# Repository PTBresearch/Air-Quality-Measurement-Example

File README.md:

# Note: This repository is meant as an example. The code is incomplete and not the latest version. 

# Note: The global InfluxDB instance is planned to be replaced by Fiware.

# Air Quality

## Sensors List (Not Complete)

+ **PPD42NS** (Dust Concentration)

+ **BME280** (Humidity, Air Pressure, Temperature)

+ **CCS811** (TVOC Value, CO2 Equivalent)

+ **MAX31855PMB1#** (Temperature)

+ **SHT35** (Temperature, Humidity)

+ **GUVA-S12D** (UV)

+ **TCS34725** Light Sensor (RGB, Color Temperature, Brightness, Reference Value)

+ **MH-Z19C** (CO2 Value Infrared Sensor, Temperature)

+ **SPH** (DB)

+ **HP206C** ()

## Images and Render

<table>
  <tr>
    <td>
      
      <figcaption>Blender Case with PCB Render</figcaption>
    </td>
    <td>
      
      <figcaption>Blender Base with PCB Render</figcaption>
    </td>
    <td>
      
      <figcaption>Blender PCB Render</figcaption>
    </td>
  </tr>
  <tr>
    <td>
      
      <figcaption>Full Top</figcaption>
    </td>
    <td>
      
      <figcaption>Full Front</figcaption>
    </td>
    <td>
      
      <figcaption>Sensor Station</figcaption>
    </td>
  </tr>
  <tr>
    <td>
      
      <figcaption>Open PCB V1</figcaption>
    </td>
    <td>
      
      <figcaption>Front View</figcaption>
    </td>
    <td>
      
      <figcaption>Side View</figcaption>
    </td>
  </tr>
</table>

## Structure

```
.
├── Arduino-Code/          # The main folder for all microcontroller code.
│   ├── Main/              # Code for the primary Arduino prototype (likely ESP8266).
│   │   ├── lib/           # Libraries for this specific project.
│   │   └── Main.ino # The main program file for the Arduino.
│
├── Dokumentation/         # Images.
│
├── Files/                 # Specific files relevant to hardware and measurements.
│   ├── Gehaeuse/          # 3D models and design files for the project's enclosure.
│   └── Platinen/          # Design files (Gerber files, etc.) for the printed circuit boards (PCBs).
│
└── Raspberry-Installer/   # Scripts and files for setting up the Raspberry Pi.
    └── Docker/            # Docker configurations and source code for installing services on the Pi.
        └── src/           # Source code used by the Docker containers.
```

## Function

```
┌── Raspberry Pi
│   └── Creates a Wi-Fi network
│
└── Arduino
    ├── Connects to the Wi-Fi network
    │
    ├── Reads data from the sensor
    │
    └── Sends data over Wi-Fi to the API
        │
        └── API
            ├── Collects the sent data
            │
            ├── Inserts the data into a local database (InfluxDB)
            │
            └── Inserts the data into a global database (InfluxDB)
```

## Example JSON-Structure

```
{
  "arduino_board": "<arduino_id>",
  "sensors": [
    {
      "name": "<sensor_name>",
      "sensor_model": "<sensor_model>",
      "readings": [
        {
          "type": "<influx measurement>",
          "value": VALUE,
          "unit": "<unit>"
          "label": "<label optional>"
        },
        {
          "type": "<influx measurement>",
          "value": VALUE,
          "unit": "<unit>"
          "label": "<label optional>"
        }
      ]
    },
    {
      "name": "bme280",
      "sensor_model": "",
      "readings": [
        {
          "type": "temperature",
          "value": VALUE,
          "unit": "celsius"
        },
        {
          "type": "pressure",
          "value": VALUE,
          "unit": "hpa"
        },
        {
          "type": "humidity",
          "value": VALUE,
          "unit": "%"
        }
      ]
    }
  ]
}
```

---

## Instalation

1. Download: 

```bash
git clone <url> luftqualitaet
```

2. Edit ```WLAN_SSID``` in ```luftqualitaet/Raspberry-Installer/config.sh``` 
```bash
export replace=<Hostname>
sed -i -e 's/WLAN_SSID = Hostname/WLAN_SSID = ${replace}/g' luftqualitaet/Raspberry-Installer/config.sh
```

3. (Optional) Set Proxy Settings ```luftqualitaet/Raspberry-Installer/Docker/.env```
```bash
echo "http_proxy=http://webproxy:8080
https_proxy=http://webproxy:8080
no_proxy=influx,localhost" > /home/pi/luftqualitaet/Raspberry-Installer/Docker/.env
```

4. Login as Root
```bash
sudo -i
```

5. Change directory to Installer Location
```bash
cd /home/pi/luftqualitaet/Raspberry-Installer
```

6. Make Script executeable
```bash
chmod +x config.sh setup.sh
```

7. Set Current Time
```bash
HTTP_DATE=$(curl -x http://webproxy:8080  -ksI 'https://ptb.de' | grep -i '^date:' | sed 's/Date: //i' | sed 's/ (GMT)//')
if [ -n "$HTTP_DATE" ]; then date -s "$HTTP_DATE" && echo "Systemzeit erfolgreich gesetzt."; else echo "WARNUNG: Konnte die Zeit nicht über HTTP abrufen."; fi
```

8. Run Script
```
./setup.sh
```

9. Change directory to Docker Location
```bash
cd /home/pi/luftqualitaet/Raspberry-Installer/Docker
```

10. Start Docker
```bash
docker compose up -d
```

11. Setup Influxdb (http://hostname:8086) and Grafan (http://hostname:3000) 

12. Set InfluxDB Token in Config ```/home/pi/Raspberry-Installer/Docker/src/config.yml````

13. Restart Docker
```bash
docker compose down
docker compose up -d
```

14. Restart Raspberry PI
```bash
systemctl reboot
```

---

## Components

### Raspberry PI

| Component | Order Link | Datasheet Link(s) | Further Information |
|---|---|---|---|
| Pi 4B | [https://www.reichelt.de/das-reichelt-raspberry-pi-4-b-4-gb-all-in-bundle-rpi-4b-4gb-allin-p263086.html](https://www.reichelt.de/das-reichelt-raspberry-pi-4-b-4-gb-all-in-bundle-rpi-4b-4gb-allin-p263086.html) | | |
| Micro SD | [https://www.reichelt.de/de/de/shop/produkt/microsdxc-speicherkarte_128gb_samsung_pro_plus-313955](https://www.reichelt.de/de/de/shop/produkt/microsdxc-speicherkarte_128gb_samsung_pro_plus-313955) | | |
| GPS | [https://www.reichelt.de/de/de/shop/produkt/raspberry_pi_shield_-_multi-gnss_l76x-266060](https://www.reichelt.de/de/de/shop/produkt/raspberry_pi_shield_-_multi-gnss_l76x-266060) | | |
| Raspberry Pi Shield | [https://www.reichelt.de/de/de/shop/produkt/raspberry_pi_shield_-_display_lcd-touch_7_800x480_pixel-282508](https://www.reichelt.de/de/de/shop/produkt/raspberry_pi_shield_-_display_lcd-touch_7_800x480_pixel-282508) | | |

### Sensor Station

| Component | Sensor Type | Order Link | Datasheet Link(s) | Notes | Ambient Temperature | Humidity | Air Pressure |
|---|---|---|---|---|---|---|---|
| **BME280** | Temp & Pressure Sensor | [https://www.reichelt.de/ch/de/shop/produkt/entwicklerboards\_-\_temperatur-\_feuchtigkeits-*und\_drucksensor*-253982](https://www.reichelt.de/ch/de/shop/produkt/entwicklerboards_-_temperatur-_feuchtigkeits-_und_drucksensor_-253982) | [https://cdn-reichelt.de/documents/datenblatt/A300/BST-BME280-DS002-1509607.pdf](https://cdn-reichelt.de/documents/datenblatt/A300/BST-BME280-DS002-1509607.pdf) | Inaccurate temperature (error tolerance of +3°C) | Accuracy: +1.0°C \<br\> Range: -40°C to +85°C \<br\> Max Deviation: Up to +1.5°C | Accuracy: +3% rF \<br\> Range: 0% to 100% rF \<br\> Max Deviation: up to +5% | Accuracy: +1 hPa \<br\> Range: 300 hPa \<br\> Max Deviation: Up to +1.7 hPa |
| **CCS811** | TVOC | [https://www.reichelt.de/ch/de/shop/produkt/entwicklerboards\_-\_sensor\_fuer\_luftqualitaet\_ccs811-253655](https://www.reichelt.de/ch/de/shop/produkt/entwicklerboards_-_sensor_fuer_luftqualitaet_ccs811-253655) | [https://cdn-reichelt.de/documents/datenblatt/A300/SEN-CCS811V1-DATENBLATT-02-11-2020.pdf](https://cdn-reichelt.de/documents/datenblatt/A300/SEN-CCS811V1-DATENBLATT-02-11-2020.pdf) | Has a burn-in period (48 hours) and a warm-up time (20 min) before it becomes accurate | Accuracy: +3°C \<br\> Range: 0°C to +50°C \<br\> Max Deviation: approx. +5°C | Range: 10% to 95% | |
| **PPD42NS** | Dust | [https://www.reichelt.de/ch/de/shop/produkt/arduino\_-\_staubsensor\_ppd42ns-191264](https://www.reichelt.de/ch/de/shop/produkt/arduino_-_staubsensor_ppd42ns-191264) | [https://cdn-reichelt.de/documents/datenblatt/A300/101020012\_01.pdf](https://cdn-reichelt.de/documents/datenblatt/A300/101020012_01.pdf) | Must be straight, requires 3 min to warm up, arbitrary operation can lead to damage, standard settings should not be changed | Recommended Range: -10°C to +65°C | Range: 0% to 70% | |
| **MAX31855PMB1\#** | Typk Temp | [https://de.farnell.com/analog-devices/max31855pmb1/peripheriemodul-thermoel-digit/dp/2530496](https://de.farnell.com/analog-devices/max31855pmb1/peripheriemodul-thermoel-digit/dp/2530496) | [https://www.farnell.com/datasheets/2025616.pdf](https://www.farnell.com/datasheets/2025616.pdf) | Inaccurate temperature (error tolerance of +2°C) | Recommended Range: -20°C to +85°C | Range: 0% to 95% | |
| **D1 Mini** | D1 Mini | [https://www.reichelt.de/de/de/shop/produkt/d1\_mini\_-\_kompatibles\_esp8266\_board\_v2\_0-253978](https://www.reichelt.de/de/de/shop/produkt/d1_mini_-_kompatibles_esp8266_board_v2_0-253978) | | | | | |
| **D1 Mini** | D1 Mini Pro | https:www.reichelt.de/de/de/shop/produkt/d1\_mini\_pro\_-\_kompatibles\_esp8266\_board\_cp2104-266066 | | | | | |
| **Power Supply** | Breadboard | [https://www.reichelt.de/de/de/shop/produkt/entwicklerboards\_-\_spannungsversorgung\_f\_steckboards-202832](https://www.reichelt.de/de/de/shop/produkt/entwicklerboards_-_spannungsversorgung_f_steckboards-202832) | [https://cdn-reichelt.de/documents/datenblatt/A300/DATENBLATTSBC-POW-BB.pdf](https://cdn-reichelt.de/documents/datenblatt/A300/DATENBLATTSBC-POW-BB.pdf) | Too high voltage can damage the device or even lead to a fire | Recommended Range: 0°C to +70°C | Range: 10% to 60% (Absolutely not intended for humid rooms) | |
| **GSM18E09-P1J** | Plug-in Power Supply | [https://www.conrad.de/de/p/mean-well-gsm18e09-p1j-steckernetzteil-festspannung-9-v-dc-2-a-18-w-1837961.html](https://www.conrad.de/de/p/mean-well-gsm18e09-p1j-steckernetzteil-festspannung-9-v-dc-2-a-18-w-1837961.html) | [https://asset.conrad.com/media10/add/160267/c1/-/en/001837961DS01/datenblatt-1837961-mean-well-gsm18e09-p1j-steckernetzteil-festspannung-9-vdc-2-a-18-w.pdf](https://asset.conrad.com/media10/add/160267/c1/-/en/001837961DS01/datenblatt-1837961-mean-well-gsm18e09-p1j-steckernetzteil-festspannung-9-vdc-2-a-18-w.pdf) | Only lasts 3 years and is only 88% efficient | Recommended Range: -25 to +60 | Range: 20% to 90% | |
| **SHT35** | Temp & Humidity | [https://de.farnell.com/seeed-studio/101020212/sensorplatine-arduino-board/dp/3932104](https://de.farnell.com/seeed-studio/101020212/sensorplatine-arduino-board/dp/3932104) | [https://www.farnell.com/datasheets/3708357.pdf](https://www.farnell.com/datasheets/3708357.pdf) | Environmentally sensitive and should not be touched with fingers as it can be damaged | Recommended Range: -40°C to 125°C | Range: 10% to 90% | |
| **ADC** | Analog Digital Converter | [https://www.conrad.de/de/p/joy-it-ky053adc-raspberry-pi-erweiterungs-platine-passend-fuer-einplatinen-computer-raspberry-pi-raspberry-pi-a-b-1656368.html](https://www.conrad.de/de/p/joy-it-ky053adc-raspberry-pi-erweiterungs-platine-passend-fuer-einplatinen-computer-raspberry-pi-raspberry-pi-a-b-1656368.html) | [https://asset.conrad.com/media10/add/160267/c1/-/de/001656368DS01/datenblatt-1656368-joy-it-ky053adc-raspberry-pi-erweiterungs-platine-passend-fuer-einplatinen-computer-raspberry-pi-raspberry-pi-a-b.pdf](https://asset.conrad.com/media10/add/160267/c1/-/de/001656368DS01/datenblatt-1656368-joy-it-ky053adc-raspberry-pi-erweiterungs-platine-passend-fuer-einplatinen-computer-raspberry-pi-raspberry-pi-a-b.pdf) | Sensitive to interference due to its high resolution, which can make it slower to measure rapidly changing signals or values | Recommended Range: -40°C to 125°C | Range: 0% to 95% | |
| **GUVA-S12D** | UV Sensor | [https://www.reichelt.de/de/de/shop/produkt/arduino\_-\_uv-sensor\_guva-s12d-191215](https://www.reichelt.de/de/de/shop/produkt/arduino_-_uv-sensor_guva-s12d-191215) | [https://cdn-reichelt.de/documents/datenblatt/A300/101020043\_01.pdf](https://cdn-reichelt.de/documents/datenblatt/A300/101020043_01.pdf) | Can be altered by temperature, sensitive to environmental influences, not precise | Recommended Range: -30°C to +85°C | Range: 0% to 95% | |
| **TCS34725** | Light Sensor | [https://www.conrad.de/de/p/az-delivery-tcs34725-rgb-farb-sensor-mit-infrarot-filter-diy-modul-zur-farb-erkennung-kompatibel-mit-arduino-850037694.html](https://www.conrad.de/de/p/az-delivery-tcs34725-rgb-farb-sensor-mit-infrarot-filter-diy-modul-zur-farb-erkennung-kompatibel-mit-arduino-850037694.html) | [https://ams-osram.com/products/sensor-solutions/ambient-light-color-spectral-proximity-sensors/ams-tcs34725-color-sensor](https://ams-osram.com/products/sensor-solutions/ambient-light-color-spectral-proximity-sensors/ams-tcs34725-color-sensor) | Light can change measurement values, the sensor has a certain amount of background noise | Recommended Range: -40°C to +85°C | Range: 0% to 60% | |
| **MH-Z19C** | CO2 Sensor | [https://www.reichelt.de/de/de/shop/produkt/infrarot\_co2-sensor\_mh-z19c\_pinleiste\_rm\_2\_54-297320](https://www.reichelt.de/de/de/shop/produkt/infrarot_co2-sensor_mh-z19c_pinleiste_rm_2_54-297320) | [https://cdn-reichelt.de/documents/datenblatt/C150/MH-Z19CDATENBLATT.pdf](https://cdn-reichelt.de/documents/datenblatt/C150/MH-Z19CDATENBLATT.pdf) | Only works at optimal temperatures (-10 \~ 50 °C) and is sensitive to heat and sun | Recommended Range: -10°C to 50°C | Range: 0% to 95% | |
| **Teensy4.1** | Teensy4.1 | [https://www.reichelt.de/de/de/shop/produkt/teensy\_4\_1\_usb\_ohne\_header-283580](https://www.reichelt.de/de/de/shop/produkt/teensy_4_1_usb_ohne_header-283580) | [https://cdn-reichelt.de/documents/datenblatt/A300/TEENSY\_41\_DE.pdf](https://cdn-reichelt.de/documents/datenblatt/A300/TEENSY_41_DE.pdf) | Consumes a lot of power, lacks a Wi-Fi or Bluetooth connection, and can overheat during complex tasks | Recommended Range: -40°C to +85°C | Range: 0% to 95% | |
| **HP206C** | Grove - Barometer | [https://de.farnell.com/seeed-studio/101020068/sensor-barometer-arduino-raspberry/dp/4007687](https://de.farnell.com/seeed-studio/101020068/sensor-barometer-arduino-raspberry/dp/4007687) | [https://www.farnell.com/datasheets/3759062.pdf](https://www.farnell.com/datasheets/3759062.pdf) | The chip only accepts an input voltage of 1.8 V to 3.6 V. | Recommended Range: -40°C to +85°C | Range: 5% to 90% | |

### Mic

| Component | Sensor Type | Order Link | Datasheet Link(s) | Notes | Ambient Temperature | Humidity | Air Pressure |
|---|---|---|---|---|---|---|---|
| SPH0645 | Mems Mic | [https://www.reichelt.de/de/de/shop/produkt/entwicklerboards_-_mikrofone_sph0645-271874](https://www.reichelt.de/de/de/shop/produkt/entwicklerboards_-_mikrofone_sph0645-271874) | [https://cdn-reichelt.de/documents/datenblatt/A300/DEBO_MEMS_MIC_DB_EN.pdf](https://cdn-reichelt.de/documents/datenblatt/A300/DEBO_MEMS_MIC_DB_EN.pdf) | Sensitive to air, especially at the porthole (may require further investigation later) | Recommended Range: -40°C to +85°C | Range: 5% to 95% | |
| D1 Mini | D1 Mini | [https://www.reichelt.de/de/de/shop/produkt/d1_mini_-_kompatibles_esp8266_board_v2_0-253978](https://www.reichelt.de/de/de/shop/produkt/d1_mini_-_kompatibles_esp8266_board_v2_0-253978) | | | | | |
| D1 Mini | D1 Mini Pro | https:www.reichelt.de/de/de/shop/produkt/d1_mini_pro_-_kompatibles_esp8266_board_cp2104-266066 | | | | | |
| D1 Mini | D1 Mini Lite | [https://www.reichelt.de/de/de/shop/produkt/d1_mini_lite_-_kompatibles_esp8285_board-291438](https://www.reichelt.de/de/de/shop/produkt/d1_mini_lite_-_kompatibles_esp8285_board-291438) | | | | | |
| Teensy4.1 | Teensy4.1 | [https://www.reichelt.de/de/de/shop/produkt/teensy_4_1_usb_ohne_header-283580](https://www.reichelt.de/de/de/shop/produkt/teensy_4_1_usb_ohne_header-283580) | [https://cdn-reichelt.de/documents/datenblatt/A300/TEENSY_41_DE.pdf](https://cdn-reichelt.de/documents/datenblatt/A300/TEENSY_41_DE.pdf) | Consumes a lot of power, lacks a Wi-Fi or Bluetooth connection, and can overheat during complex tasks | Recommended Range: -40°C to +85°C | Range: 0% to 95% | |
| Power Supply | USB Charger | [https://www.reichelt.de/de/de/shop/produkt/usb-ladegeraet_5_v_1_a_usb-c_schwarz-268087?PROVID=2788](https://www.reichelt.de/de/de/shop/produkt/usb-ladegeraet_5_v_1_a_usb-c_schwarz-268087?PROVID=2788) | | | | | |

---

## Notes on Individual Sensors (Regarding Placement)

+ **BME280 Temperature, Air Pressure, Humidity Sensor:**
    + [https://www.makershop.de/download/bst-bme280-ds002.pdf](https://www.makershop.de/download/bst-bme280-ds002.pdf)
    + Do not place near heaters.

+ **CCS811 Carbon Dioxide Gas Sensor Metal Oxide:**
    + [https://www.makershop.de/download/CCS811_Datasheet-DS000459.pdf](https://www.makershop.de/download/CCS811_Datasheet-DS000459.pdf)
    + No special measures required.

+ **TCS3472 Color Sensor:**
    + [https://cdn.shopify.com/s/files/1/1509/1638/files/TCS3472_datasheet_1692bf77-3213-4bd2-9a66-8a9e70545e7e.pdf?v=1705651929](https://cdn.shopify.com/s/files/1/1509/1638/files/TCS3472_datasheet_1692bf77-3213-4bd2-9a66-8a9e70545e7e.pdf?v=1705651929)
    + The sensor should have access to light.
    + Not next to an LED on the ESP microcontroller.

+ **GRV Loudness Sensor:**
    + [https://cdn-reichelt.de/documents/datenblatt/A300/101020063_01.pdf](https://cdn-reichelt.de/documents/datenblatt/A300/101020063_01.pdf)
    + The sensor should have external access.
    + Should be able to capture ambient sound.
    + Do not place it behind a cover.

+ **GRV Dust Sensor:**
    + [https://cdn-reichelt.de/documents/datenblatt/A300/101020012_01.pdf](https://cdn-reichelt.de/documents/datenblatt/A300/101020012_01.pdf)
    + The chip on the back gets hot occasionally.
    + Has a built-in fan, so do not place it directly next to the GRV Loudness sensor.

---

## General Notes

+ The enclosure must be sufficiently open to allow air to flow in for measurements.
+ Ensure thermal, optical, and acoustic decoupling of the microcontroller from the sensors (use a partition).
+ Leave space for 2-3 additional sensors (check sensor dimensions with a reference image).
+ Leave space for 2 more ESPs (D1 Mini Lite), for a total of 3.

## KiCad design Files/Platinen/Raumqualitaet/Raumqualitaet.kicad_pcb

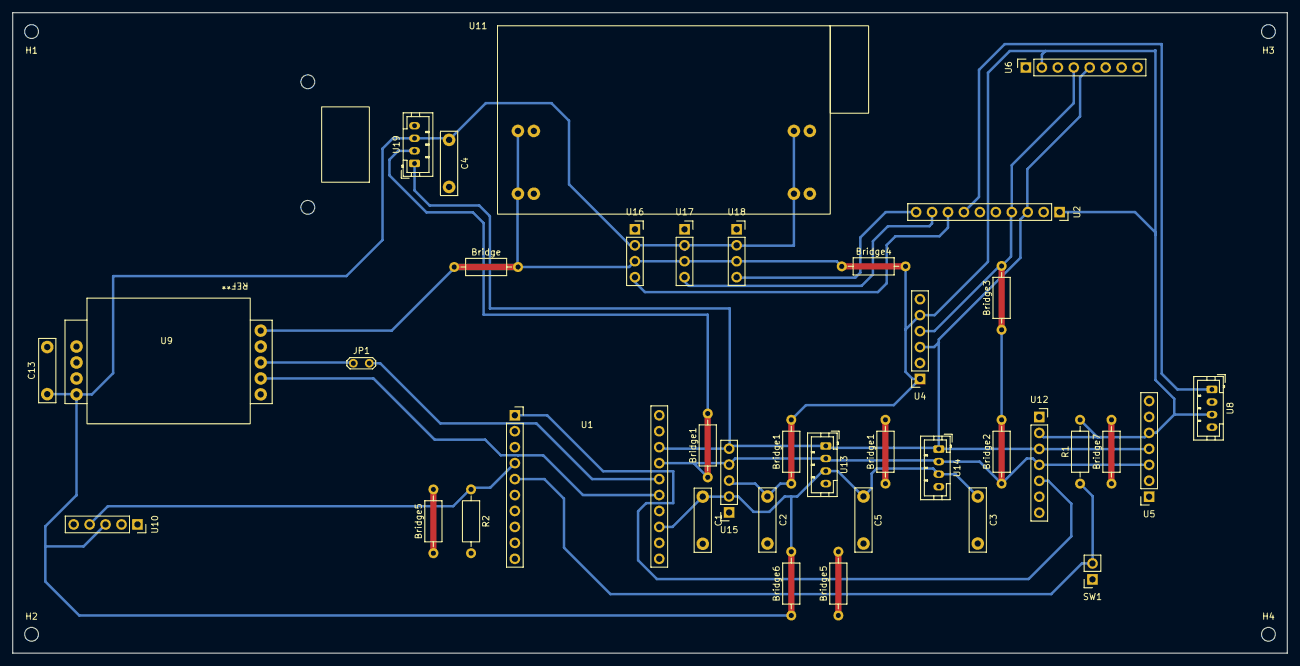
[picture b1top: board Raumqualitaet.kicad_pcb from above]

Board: 2 copper layers, 203.0 x 102.0 mm, 42 parts (0 on the bottom side), 15 nets.

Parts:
Bridge: Bridge; R_Axial_DIN0207_L6.3mm_D2.5mm_P10.16mm_Horizontal
Bridge1, Bridge1#2, Bridge1#3: Bridge:1; R_Axial_DIN0207_L6.3mm_D2.5mm_P10.16mm_Horizontal
Bridge2: Bridge2; R_Axial_DIN0207_L6.3mm_D2.5mm_P10.16mm_Horizontal
Bridge3: Bridge3; R_Axial_DIN0207_L6.3mm_D2.5mm_P10.16mm_Horizontal
Bridge4: Bridge4; R_Axial_DIN0207_L6.3mm_D2.5mm_P10.16mm_Horizontal
Bridge5, Bridge5#2: Bridge5; R_Axial_DIN0207_L6.3mm_D2.5mm_P10.16mm_Horizontal
Bridge6: Bridge6; R_Axial_DIN0207_L6.3mm_D2.5mm_P10.16mm_Horizontal
Bridge7: Bridge7; R_Axial_DIN0207_L6.3mm_D2.5mm_P10.16mm_Horizontal
C1, C2, C3, C4, C5, C13: 100n; C_Rect_L10.0mm_W2.5mm_P7.50mm_MKS4
H1, H2, H3, H4: MountingHole; MountingHole_2.2mm_M2_DIN965
JP1: Jumper_2_Bridged; Jumper_2.54mm
R1: 10k; R_Axial_DIN0207_L6.3mm_D2.5mm_P10.16mm_Horizontal
R2: R; R_Axial_DIN0207_L6.3mm_D2.5mm_P10.16mm_Horizontal
SW1: SW_Push; PinSocket_1x02_P2.54mm_Vertical
U1: WeMos_D1_mini; ESP32_D1
U2: KY053ADC; PinSocket_1x10_P2.54mm_Vertical
U4: BMP280; PinSocket_1x06_P2.54mm_Vertical
U5: TCS3472; PinSocket_1x07_P2.54mm_Vertical
U6: SEN-CCS811; PinSocket_1x08_P2.54mm_Vertical
U8: UV - Pin 1 as Data; JST_PH_B4B-PH-K_1x04_P2.00mm_Vertical
U9: MH-Z19C
U10: PPD42; PinSocket_1x05_P2.54mm_Vertical
U11: SBC-POW-BB
U12: Display; PinSocket_1x07_P2.54mm_Vertical
U13, U14, U19: Grove Device; JST_PH_B4B-PH-K_1x04_P2.00mm_Vertical
U15: I2C_Device; PinSocket_1x05_P2.54mm_Vertical
U16, U17, U18: Analog_Device; PinSocket_1x04_P2.54mm_Vertical

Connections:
+3V3: Bridge.1, Bridge.2, Bridge1#3.1, Bridge1#3.2, Bridge4.1, Bridge4.2, C2.1, R1.2, U2.1 (VCC), U4.1 (VCC), U4.5 (CSB), U5.5 (3V3), U6.2 (3V3), U8.3 (5V), U9.9 (HD), U11.1 (3V3), U11.2 (3V3), U12.2 (3V3), U15.3 (3V3), U16.3 (3V3), U17.3 (3V3), U18.3 (3V3)
+5V: Bridge6.1, Bridge6.2, C1.1, C3.1, C4.1, C5.1, C13.1, U1.9 (5V), U9.4 (VCC), U10.3 (VCC), U11.5 (5V), U11.6 (5V), U13.3 (5V), U14.3 (5V), U15.2 (5V), U16.2 (5V), U17.2 (5V), U18.2 (5V), U19.3 (5V)
A0: U2.7 (A0), U8.1 (Analog)
A1: U2.8 (A1), U16.4 (Signal)
A2: U2.9 (A2), U17.4 (Signal)
A3: U2.10 (A3), U18.4 (Signal)
D3: JP1.2 (B), U1.12 (D3)
D4: U1.11 (D4), U9.6 (Rx)
D5: R2.1, U1.4 (SCK/D5), U10.4 (Output_(P1))
D6: R1.1, SW1.2, U1.5 (MISO/D6)
GND: Bridge1.1, Bridge1.2, Bridge5.1, Bridge5.2, Bridge5#2.1, Bridge5#2.2, Bridge7.1, Bridge7.2, C1.2, C2.2, C3.2, C4.2, C5.2, C13.2, R2.2, SW1.1, U1.10 (GND), U2.2 (GND), U4.2 (GND), U4.6 (SDO), U5.1 (LED), U5.6 (GND), U6.3 (GND), U6.6 (WAKE), U8.4 (GND), U9.3 (GND), U10.1 (GND), U11.3 (GND), U11.4 (GND), U11.7 (GND), U11.8 (GND), U12.1 (GND), U12.6 (Dc), U12.7 (Cs), U13.4 (GND), U14.4 (GND), U15.1 (GND), U16.1 (GND), U17.1 (GND), U18.1 (GND), U19.4 (GND)
unnamed: JP1.1 (A), U9.7 (Tx)
RST: U1.1 (~RST), U12.5 (RES)
SCL: U1.14 (SCL/D1), U2.3 (SCL), U4.3 (SCL), U5.4 (SCL), U6.5 (SCL), U12.3 (SCL), U13.1 (SCL), U14.1 (SCL), U15.5 (SCL), U19.1 (SCL)
SDA: Bridge1#2.1, Bridge1#2.2, Bridge2.1, Bridge2.2, Bridge3.1, Bridge3.2, U1.13 (SDA/D2), U2.4 (SDA), U4.4 (SDA), U5.3 (SDA), U6.4 (SDA), U12.4 (SDA), U13.2 (SDA), U14.2 (SDA), U15.4 (SDA), U19.2 (SDA)

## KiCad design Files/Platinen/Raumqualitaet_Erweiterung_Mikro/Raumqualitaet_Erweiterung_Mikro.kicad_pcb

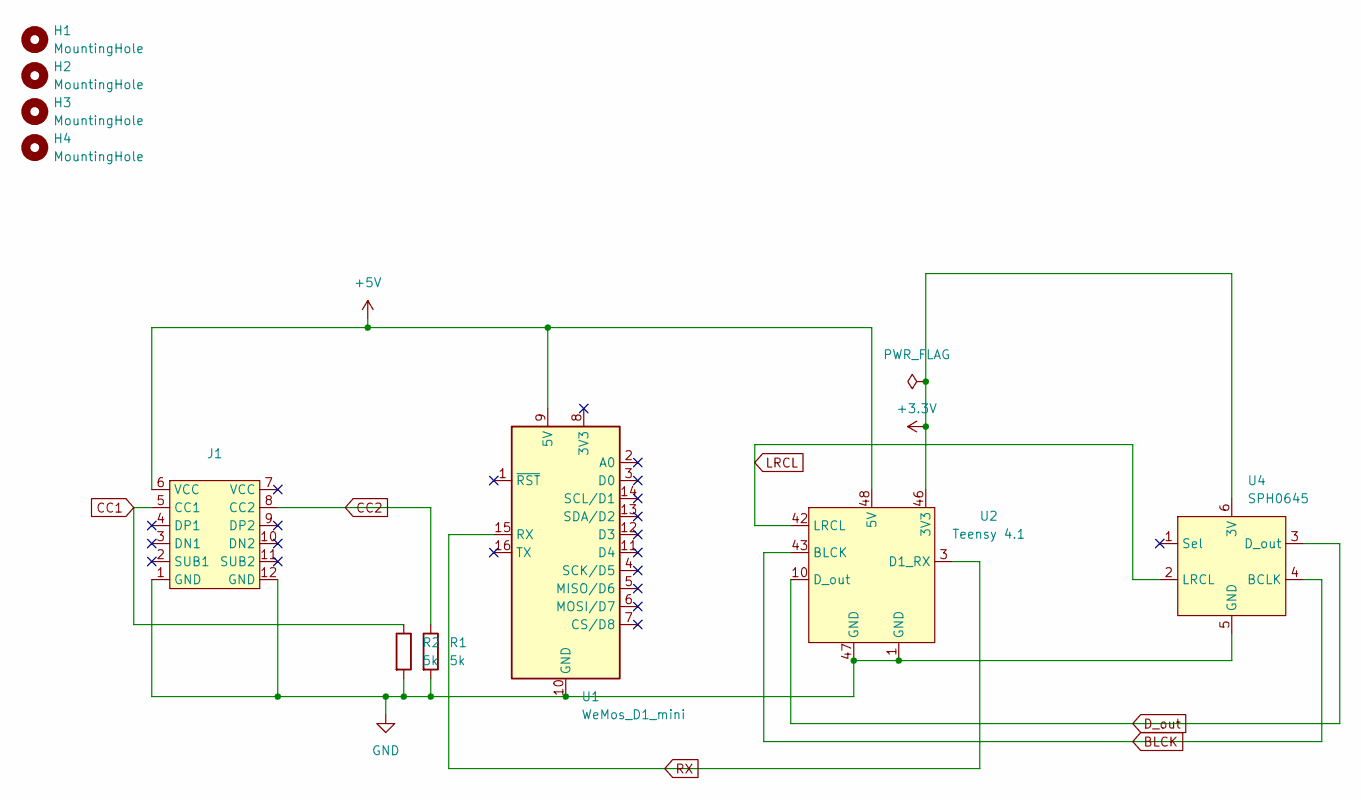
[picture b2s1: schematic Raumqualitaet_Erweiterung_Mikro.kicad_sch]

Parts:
H1, H2, H3, H4: MountingHole; MountingHole_2.2mm_M2_DIN965
J1: USB-C-DR-YM-726
R1, R2: 5k; R_Axial_DIN0207_L6.3mm_D2.5mm_P10.16mm_Horizontal
U1: WeMos_D1_mini; WEMOS_D1_mini_light
U2: Teensy 4.1; Teensy
U4: SPH0645; PinSocket_1x06_P2.54mm_Vertical

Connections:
+3.3V: U2.46 (3V3), U4.6 (3V)
+5V: J1.6 (VCC), U1.9 (5V), U2.48 (5V)
BLCK: U2.43 (BLCK), U4.4 (BCLK)
CC1: J1.5 (CC1), R2.1
CC2: J1.8 (CC2), R1.1
D_out: U2.10 (D_out), U4.3 (D_out)
GND: J1.1 (GND), J1.12 (GND), R1.2, R2.2, U1.10 (GND), U2.1 (GND), U2.47 (GND), U4.5 (GND)
LRCL: U2.42 (LRCL), U4.2 (LRCL)
RX: U1.15 (RX), U2.3 (D1_RX)

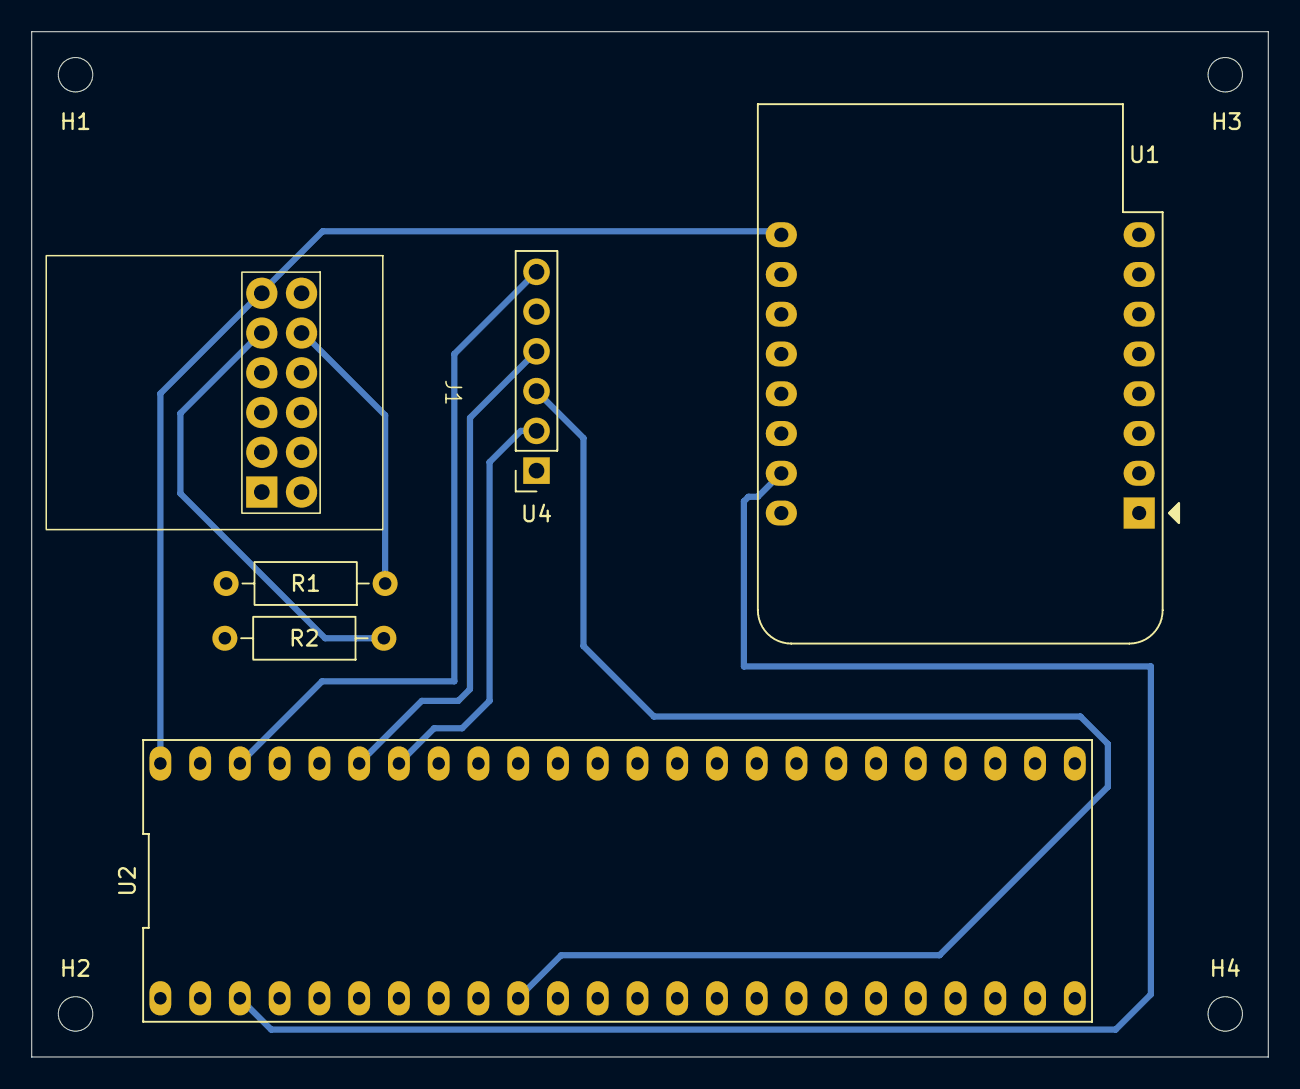
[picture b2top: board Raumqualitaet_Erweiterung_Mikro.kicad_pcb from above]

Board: 2 copper layers, 79.0 x 65.5 mm, 10 parts (0 on the bottom side), 9 nets.

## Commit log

2025-09-16 Create LICENSE
2025-09-16 update images
